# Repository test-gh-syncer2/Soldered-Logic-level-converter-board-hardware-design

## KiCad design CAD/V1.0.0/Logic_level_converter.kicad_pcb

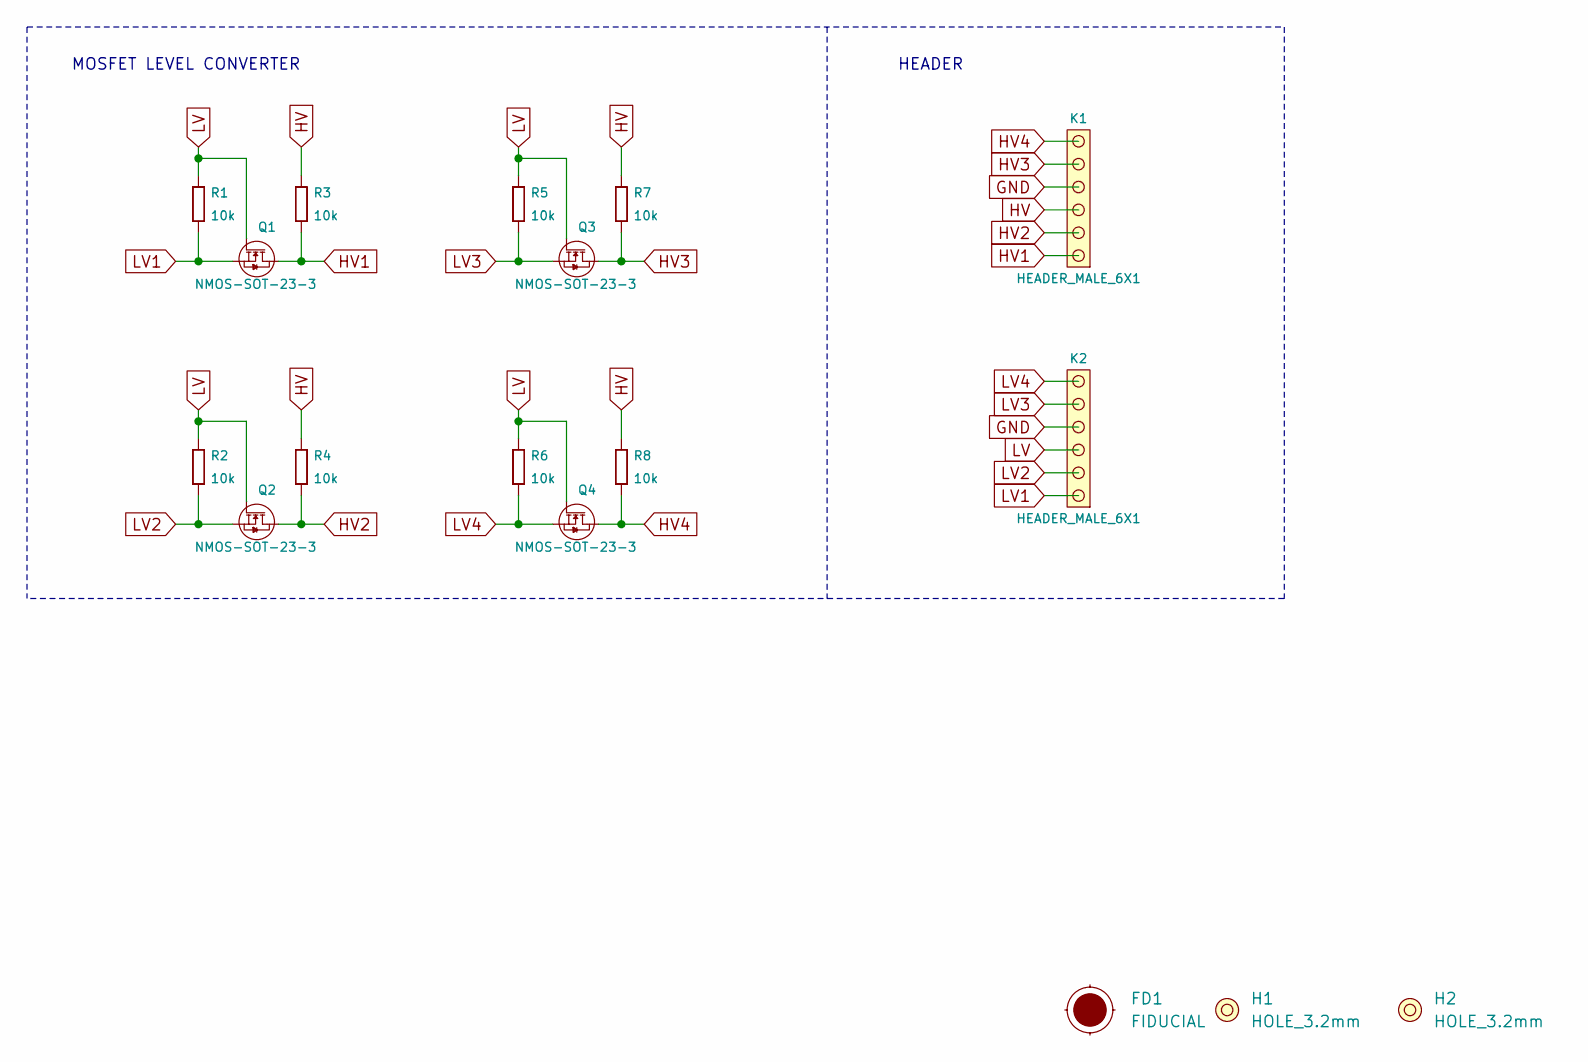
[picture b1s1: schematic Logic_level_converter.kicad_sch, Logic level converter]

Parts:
FD1: FIDUCIAL; FIDUCIAL_23
H1, H2: HOLE_3.2mm
K1, K2: HEADER_MALE_6X1
Q1, Q2, Q3, Q4: NMOS-SOT-23-3; SOT-23-3
R1, R2, R3, R4, R5, R6, R7, R8: 10k; 0603R

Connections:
GND: K1.4, K2.4
HV: K1.3, R3.2, R4.2, R7.2, R8.2
HV1: K1.1, Q1.3 (D), R3.1
HV2: K1.2, Q2.3 (D), R4.1
HV3: K1.5, Q3.3 (D), R7.1
HV4: K1.6, Q4.3 (D), R8.1
LV: K2.3, Q1.1 (G), Q2.1 (G), Q3.1 (G), Q4.1 (G), R1.2, R2.2, R5.2, R6.2
LV1: K2.1, Q1.2 (S), R1.1
LV2: K2.2, Q2.2 (S), R2.1
LV3: K2.5, Q3.2 (S), R5.1
LV4: K2.6, Q4.2 (S), R6.1

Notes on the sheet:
MOSFET LEVEL CONVERTER
HEADER

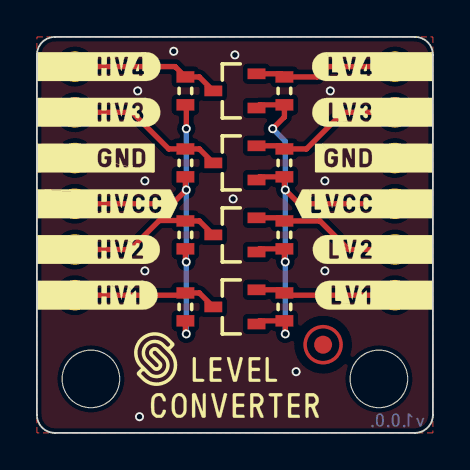
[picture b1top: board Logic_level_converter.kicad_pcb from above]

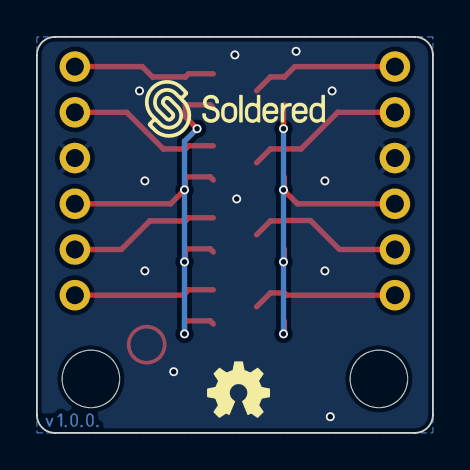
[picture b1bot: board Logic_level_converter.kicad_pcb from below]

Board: 2 copper layers, 22.0 x 22.0 mm, 17 parts (2 on the bottom side), 11 nets.

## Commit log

2021-09-23 Syncing to git
2021-09-23 Updating open source files.
